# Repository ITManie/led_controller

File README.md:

# 

Arduino project to control RGB LED strip

## Part list
 - IQRF Development set [IQRF DS-START-04](http://eshop.iqrf.org/products/detail/DS-START-04)
 - IQRF Breakout board [IQRF BB-01](http://eshop.iqrf.org/products/detail/IQRF-BB-01)
 - IQRF gateway (for example [IQRF GW-ETH-02A](http://eshop.iqrf.org/products/detail/GW-ETH-02A%2872D%29))
 - Atmel MCU with Arduino firmware or Adruino (for example [Arduino Nano](http://www.tme.eu/en/details/a000005/arduino-development-kits/arduino/arduino-nano/))
 - 3x [STMicroelectronics TIP122](http://www.tme.eu/en/details/tip122/npn-tht-darlington-transistors/st-microelectronics/)
 - 5V voltage stabiliser (for example [ON Semiconductor MC78M05CTG](http://www.tme.eu/en/details/mc78m05ctg/unregulated-voltage-regulators/on-semiconductor/))
 - RGB LED strip (for example [OptoFlash OPRGB5060-6012B](http://www.tme.eu/en/details/oprgb5060-6012b/light-sources-led-ribbon/optoflash/))
 - 5,5/2,1mm DC jack (for example [CLIFF FC68148](http://www.tme.eu/en/details/fc68148/dc-power-connectors/cliff/))
 - 12V power supply (for example [ESPE ZSIDT12/3A](http://www.tme.eu/en/details/zsidt12_3a/mains-power-supplies/espe/))
 - terminal block PCB mount (for example [Degson Electronics DG300-5.0-02P-12-00A(H)](http://www.tme.eu/en/details/dg300-5.0-2p12/terminal-blocks-pcb-mount/degson-electronics/dg300-50-02p-12-00ah/))

## Arduino libraries

 * [IQRF](https://github.com/iqrfsdk/clibiqrf-arduino)
 * [MsTimer2](https://github.com/PaulStoffregen/MsTimer2)

## Packets

### Ping
<table>
<tr>
<th>0-FF</th>
<th>100-1FF</th>
<th>200-2FF</th>
<th>300-3FF</th>
<th>400-4FF</th>
<th>500-5FF</th>
</tr>
<tr>
<td>version</td>
<td>type</td>
<td colspan="4">address</td>
</tr>
<tr>
<td>0</td>
<td>0</td>
<td>0-FF</td>
<td>0-FF</td>
<td>0-FF</td>
<td>0-FF</td>
</tr>
</table>

### Pong
<table>
<tr>
<th>0-FF</th>
<th>100-1FF</th>
<th>200-2FF</th>
<th>300-3FF</th>
<th>400-4FF</th>
<th>500-5FF</th>
</tr>
<tr>
<td>version</td>
<td>type</td>
<td colspan="4">address</td>
</tr>
<tr>
<td>0</td>
<td>1</td>
<td>0-FF</td>
<td>0-FF</td>
<td>0-FF</td>
<td>0-FF</td>
</tr>
</table>

### Set color
<table>
<tr>
<th>00-FF</th>
<th>100-1FF</th>
<th>200-2FF</th>
<th>300-3FF</th>
<th>400-4FF</th>
<th>500-5FF</th>
<th>600-6FF</th>
<th>700-7FF</th>
<th>800-8FF</th>
<th>900-9FF</th>
</tr>
<tr>
<td>version</td>
<td>type</td>
<td colspan="4">address</td>
<td>red</td>
<td>green</td>
<td>blue</td>
<td>alpha</td>
</tr>
<tr>
<td>0</td>
<td>2</td>
<td>0-FF</td>
<td>0-FF</td>
<td>0-FF</td>
<td>0-FF</td>
<td>0-FF</td>
<td>0-FF</td>
<td>0-FF</td>
<td>0-1</td>
</tr>
</table>

## Schema
### Prototype

### Production

## License
led-controller is licensed under the GPLv3 license:

 > Copyright (C) 2016 Roman Ondráček
 > 
 > This program is free software: you can redistribute it and/or modify
 > it under the terms of the GNU General Public License as published by
 > the Free Software Foundation, either version 3 of the License, or
 > (at your option) any later version.
 > 
 > This program is distributed in the hope that it will be useful,
 > but WITHOUT ANY WARRANTY; without even the implied warranty of
 > MERCHANTABILITY or FITNESS FOR A PARTICULAR PURPOSE.  See the
 > GNU General Public License for more details.
 > 
 > You should have received a copy of the GNU General Public License
 > along with this program.  If not, see <http://www.gnu.org/licenses/>.

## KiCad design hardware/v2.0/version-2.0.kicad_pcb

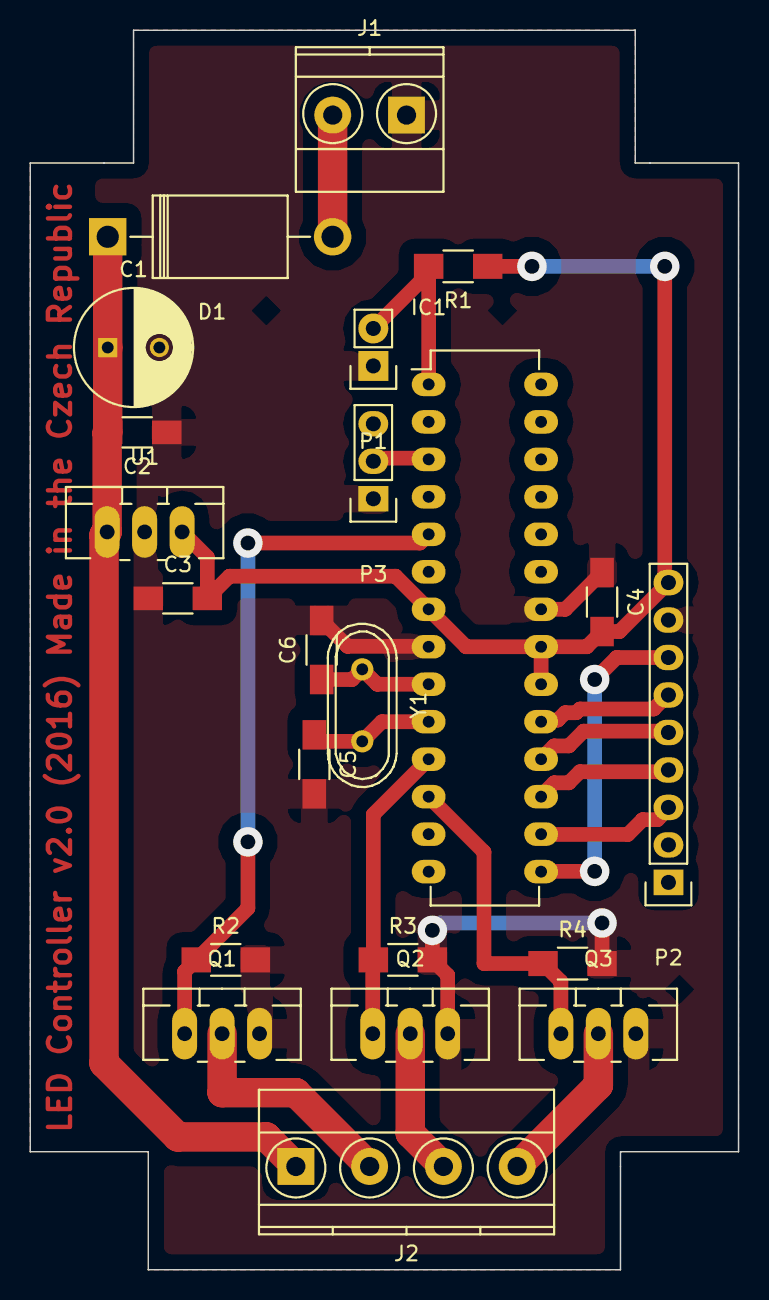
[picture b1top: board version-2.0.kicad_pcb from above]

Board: 2 copper layers, 48.0 x 84.0 mm, 22 parts (0 on the bottom side), 20 nets.

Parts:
C1: 470u; C_Radial_D8_L11.5_P3.5
C2, C3, C4: 100n; C_1206_HandSoldering
C5, C6: 18p; C_1206_HandSoldering
D1: BY550-400; Diode_DO-201AD_Horizontal_RM15
IC1: ATMEGA328P-P; DIP-28_W7.62mm_LongPads
J1: DG300-5.0; TerminalBlock_Pheonix_MKDS1.5-2pol
J2: RGB LED; TerminalBlock_Pheonix_MKDS1.5-4pol
P1: CONN_01X02; Pin_Header_Straight_1x02
P2: IQRF BB-01; Pin_Header_Straight_1x09
P3: UART; Pin_Header_Straight_1x03
Q1, Q2, Q3: IRLB8721PBF; TO-220_Neutral123_Vertical_LargePads
R1, R2, R3, R4: 10k; R_1206_HandSoldering
U1: MC78M05CTG; TO-220_Neutral123_Vertical_LargePads
Y1: CRYSTAL; Crystal_HC49-U_Vertical

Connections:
+5V: C3.2, C4.2, IC1.7, IC1.20, IC1.21, P2.9, R1.1, U1.3
+12V: C1.1, C2.2, D1.1, J2.1, U1.1
/MISO: IC1.18, P2.5
/MOSI: IC1.17, P2.4
/RX: IC1.2, P3.3
/SCK: IC1.19, P2.6
/SS: IC1.16, P2.3
/TR_RESET: IC1.15, P2.7
/TX: IC1.3, P3.2
GND: C1.2, C2.1, C3.1, C4.1, C5.2, C6.2, IC1.8, IC1.22, J1.1, P1.1, P2.8, P3.1, Q1.3, Q2.3, Q3.3, R2.2, R3.2, R4.2, U1.2
unnamed: C5.1, IC1.10, Y1.2
unnamed: C6.1, IC1.9, Y1.1
unnamed: D1.2, J1.2
unnamed: IC1.1, P1.2, R1.2
unnamed: IC1.5, Q1.1, R2.1
unnamed: IC1.11, Q2.1, R3.1
unnamed: IC1.12, Q3.1, R4.1
unnamed: J2.2, Q1.2
unnamed: J2.3, Q2.2
unnamed: J2.4, Q3.2

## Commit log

2016-01-31 Added Read me
2016-01-31 Added Travis CI configuration
2016-01-31 Added Arduino project source code
2016-01-31 Added Platform.io config
2016-01-31 Added MsTimer2 library for platform.io
2016-01-31 Edit Travis CI configuration
2016-01-31 Fix syntax error in Arduino sources
2016-01-31 Fix other syntax error in Arduino project
2016-02-01 Added libraries to Read me and delete libraries from src dir
2016-02-01 Update Plarform.io config
2016-02-01 Replace library MsTimer2 files to platformio installation
2016-02-01 Add IQRF lib register
2016-02-01 Added TODO
2016-02-01 Added libraries to sketch
2016-02-02 Replace IQRF library files to platformio installation
2016-02-02 Rename src to arduino, rename repository
2016-02-02 Edited Read me
2016-02-02 Added tested boards
2016-02-02 Remove problematic boards
2016-02-03 Added schematic and RGB LED pins
2016-02-03 Added shitty implementation of reading numbers from buffer for PWM regulation RGB LEDs
2016-02-04 Added debug informations
2016-02-04 Added skeleton for app powered by Apache Cordova
2016-02-07 Added drone.io build status
2016-02-07 Added wercker configuration
2016-02-07 Added wercker status
2016-02-07 Fix wercker configuration
2016-02-07 Fix platformio config
2016-02-07 Added GPLv3 badge
2016-02-09 Added packet structure
2016-02-10 Add Gitter badge
2016-02-10 Added Gitter badge
2016-02-10 Added sending notificatoins from Travis CI to Gitter
2016-02-10 Added implementation of setcolor packet
2016-02-19 Edited protocol diagrams
2016-02-19 Clean code
2016-02-19 Repair Travis CI configuration
2016-02-20 Added function to send pong
2016-02-20 Finished implementation of protocol
2016-02-21 Added comments to Arduino code
2016-02-21 Edit schematics in Arduino code
2016-02-23 Set LED pins as outputs
2016-02-23 Repair pinMode
2016-02-26 Added Nette skeleton for webapp
2016-03-14 [eagle] Added schematic and PCB design
2016-03-15 [Eagle] Create new board
2016-03-15 [Eagle] Update board
2016-03-16 [Eagle] Added schematic and board in pictures
2016-03-24 [Arduino] Redefine LED pins
2016-03-25 [IQRF] Added software for IQRF
2016-03-26 [README] Update name of repository
2016-03-26 [Travis CI] Remove unnecessary boards
2016-03-28 [Docs] Added skeleton of documentation for MCU letí
2016-03-28 [Wercker CI] Remove unnecessary boards
2016-03-30 [Arduino] Fix IQRF module detection
2016-03-30 [IQRF] Update sotfware for IQRF module
2016-03-31 [Arduino] Added debug infos
2016-04-13 [LICENSE] Added license header to Arduino and IQRF source code
2016-04-16 [Eagle] New schematic
2016-04-16 [Arduino] Added function to set color of RGB LED strip
2016-04-16 [webapp] Added Netbeans files to .gitignore
2016-04-17 [Docs] Changed font color from red to black
2016-04-17 [Webapp] Code format
2016-04-20 [IQRF] Update IQRF firmware
2016-04-22 [IQRF] Repaired firmware for IQRF RF module
2016-04-22 [Eagle] Added board
2016-04-24 [README] Added license
2016-04-24 [README] Added part list
2016-04-24 [README] Added schema
2016-04-24 [README] Added logo
2016-04-24 [docs] Added some informations to MCU letí 2016 ducumentation
2016-04-26 [webapp] Update dependencies
2016-04-28 [docs] Update documentation to contest MCUletí 2016
2016-04-29 [README] Update Read me (flat icon and update part list)
2016-04-29 [git] Update .gitignore
2016-04-29 [docs] Added infos about selected MCU
2016-04-29 [docs] Added some info about selected wireless module
2016-04-29 [docs] Update documentation
2016-04-30 [docs] Updated documantation
2016-04-30 [docs] Final version of documentation
2016-04-30 [docs] Added documantition in PDF format
2016-04-30 [Wercker CI] Remove configuration
2016-04-30 [Arduino] Fix bracket in condition
2016-05-04 [webapp] Update Nette framework to version 2.4
2016-05-04 [webapp] Remove adminer
2016-05-04 [webapp] Added IQRF extension to config
2016-05-05 [Eagle] Delete information file
2016-05-13 [Arduino] Clean code
2016-05-13 [Eagle] Moved prototype schema to own directory
2016-05-19 Added icon for project
2016-05-19 Formated code of SVG code of logo
2016-05-19 [GitLab CI] Added tests for Arduino code
2016-05-20 Added presentation for IQRF Contest
2016-05-20 Fixed typos in presentation
2016-05-20 Fixed other typos in presentation
2016-05-22 Added final board and schema
2016-05-22 [Eagle] Board repaired
2016-05-24 [Eagle] Edited schema and board
2016-05-24 [Eagle] Added capacitors and resistors
2016-05-25 Updated presentation in Enlish and added presentation in Czech
2016-05-25 Used official library for Arduino
2016-05-26 Fixed mirroing of PCB
2016-05-26 Fixed PCB
2016-05-26 Udated links in Read Me
2016-05-30 [Eagle] Fixed board
2016-06-02 Updated schema and board
2016-06-05 Added board to print
2016-06-08 [Arduino] Refactored source code
2016-06-08 Updated documentation to contest MCU letí 2016
2016-06-10 [Docs] Fixed grammar in documentation to MCU letí contest
2016-06-10 [Docs] Updated presentation iv Czech
2016-06-10 [Eagle] Added board and edited schema
2016-08-03 Fixed Arduino sources
2016-11-12 Remove web application from this repository
2016-11-12 Renamed eagle files
2016-11-13 Add EDA's files for version 2.0
